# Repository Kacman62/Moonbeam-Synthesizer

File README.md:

# MoonBeam Synthesizer
A standalone DAWLESS synthesizer based on a Raspberry Pi Pico. Includes a custom circuit board and codebase with the Mozzi Audio Library

# Features

- 25 multiplexed piano style keys
- Support for up to 5 notes at the same time
- 3 Analog sliders for volume pitch and vibrato
- OLED display and 2 rotary encoders with a custom code base
- Sound synthesis using the Mozzi audio library
- 4 different wave forms
- Custom ADSR editing
- Oscilloscope style waveform viewer
- Toggleable speaker and headphone out
- Audio effects and filters
- Preset sound fforms

# Initial Idea
After reading the guide from Hack club and others online to make a MIDI keyboard, it seemed like a great idea. After more research though I wanted a standalone synthesizer that does not need a computer and couldn't find many examples online. This seemed like it would be easy enough so I decided to do it myself

# Schematic and Board
The whole project is built around a raspberry pi pico 1 (a pico 2 should work too but untested). A 5x5 multiplexed array of key cap switches serve as the main input. 
On the Audio side, a PCM5100 I2S DAC is channeled into a LM4810 and LM4861 audio amplifiers, that go to a speaker and headphone jack.

The PCB was a lot more challenging, just due to the sheer size of it. It ends up being about 350mm x 90mm. But the routing wasn't too hard and I like the look of how it turned out

# Case Design
There is an included case. Currently I have not received the board so I can not confirm if it works perfectly, but I designed it around the 3D cad of the board so it should work fine. 
Only 1 of each file needs to be printed and it is assembled using M4 hardware

# Software
I initially dreaded the software but it ended up being very fun after the initial hurdles. The code is split into 2 cores, 1 for audio and 1 for the digital UI. It should work with the final assembly, all the digital has been tested, but the audio is using I2S which I can't test currently. I did use it a little bit with PWM audio and that worked fine. The waveform viewer also does show an audio signal so Im pretty confident that it will work

# UI
You navigate the UI with both rotary encoders. Double clicking either brings you into the main menu. Rotate either to select an app.
* Settings (Wrench): View current notes on each audio voice and the values of the slide potentiometers
* ADSR Editor (Envelope): Use one dial to change the level of the ADSR and the other to change the time. Changing the level of the decay, sustain and release will change the other two with it. this is intended to avoid weird audio clipping
* Wave Viewer (Wave): View the current outputted wave form. Automatically adjusts the zoom if multiple voices are playing
* Wave Changer (Square Wave): Choose from either a sin, triangle, saw, or square wave

# Art
All pixel art was created by me using Aseprite. The PK Industries and the Moonbeam synth logo are unregistered trademarks, not real companies and products, and have no legal binding on anything. I am not a lawyer, and this joke has gone on too long.

# Disclaimers
If you want to know more about the design and build process check out the journal

This project is sponsored by and made in collaboration with Hack Club, go check them out

Consider this project untested. I have put my full effort into this project and fully believe that it will work, but I have not received boards yet and thus do not know if this will work first try

# Hack Club Stuff

Estimate Total Hours: 48

My Final Total: 60.31

Your Final Total: 96.73

https://blueprint.hackclub.com/projects/928 

# Update 11/11

Huge thanks to Hack Club and the Blueprint program for assisting in this project. I have now received funding for the project and will be ordering parts. Expect future updates at the start of December

# Update 11/25

Boards have been received. Still waiting on LCSC order. Small errors have been found in the board and have been fixed in the PCB files

# Update 12/1

Boards have been assembled and multiple errors have been found. The files will still be up, but assume they do not work.
Nothing shorts together, but both the button matrix is broken, as well as the I2S DAC and amplifier not working.

# Update 12/3

After reflowing the baord, the issue has been fixed. Two of the data lines into the DAC were shorted and after fixing that, it makes sound. The code still has some issues, but they are being fixed rapidly and the current board is almost done.

# Update 12/4 

This project is now shipped. I had a lot of fun working on this, and will continue to update the software, but for now the project is in a working state so expect less updates.

# Update 12/12 

Version 1 of software is now released. This features upgrades to all parts of the code base. Numerous bug fixes, rewritten audio workflow. Support for filters, effects, and presets. Improved menus and clarity. 

# Known issues

Code: 

In settings, the note played is incorrect (going to wait for boards to arrive so I can assign keys different notes) Fixed 12/12/25

Button scanning matrix is incorrect, every button plays the same 5 notes FIXED 12/3/25

In Wave changer, the picture of the sawtooth wave is reversed from what is seen in the wave viewer

In Wave Viewer, the wave slides around randomly. (The wave is still representative of what the audio out looks like, it's just hard to focus on it)

Distortion effect is unstable and clips audio most of the time. Still able to be used in code, but not recomended

Board:

Slide pot pin spacing 2.00mm instead of 2.54mm FIXED 11/25/25

Resistor footprint 7.62mm instead of 12.04mm FIXED 11/25/25

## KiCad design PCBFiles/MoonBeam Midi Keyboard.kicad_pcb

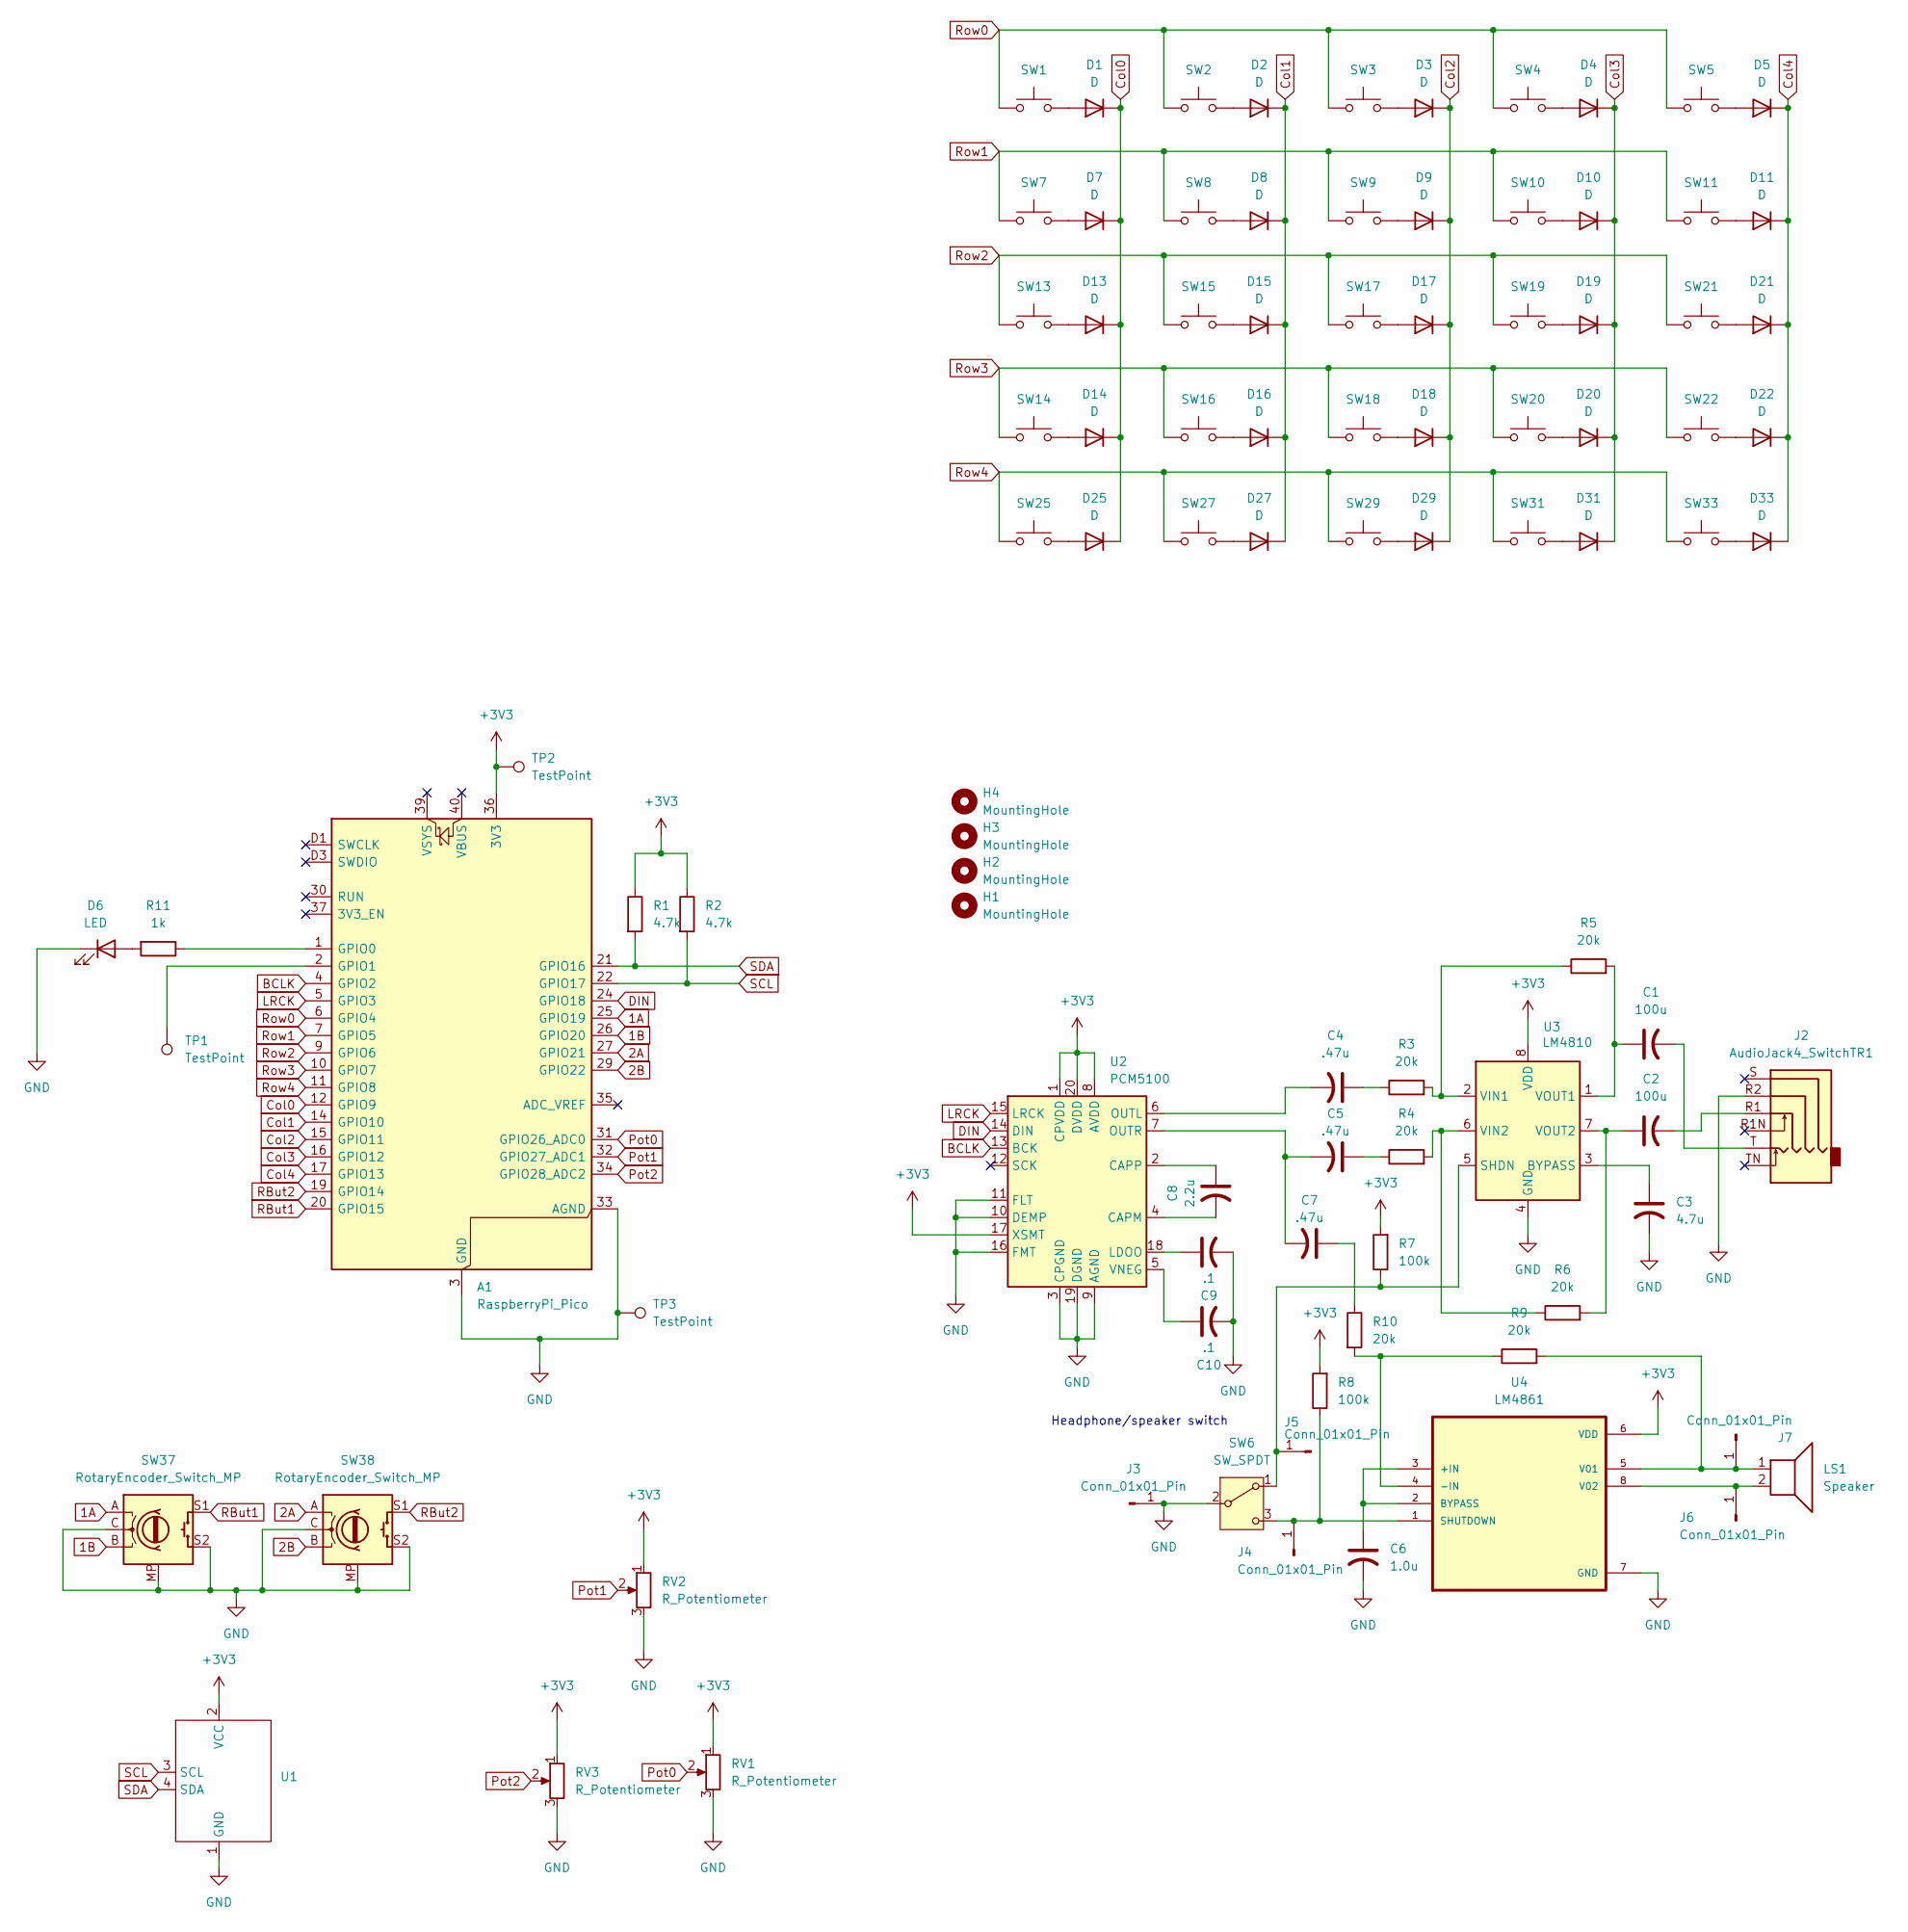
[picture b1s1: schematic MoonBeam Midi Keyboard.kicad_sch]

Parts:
A1: RaspberryPi_Pico; RaspberryPi_Pico_Common_THT
C1, C2: 100u; CP_Radial_D5.0mm_P2.50mm
C3: 4.7u; CP_Radial_D5.0mm_P2.50mm
C4, C5, C7: .47u; CP_Radial_D5.0mm_P2.50mm
C6: 1.0u; CP_Radial_D5.0mm_P2.50mm
C8: 2.2u; CP_Radial_D5.0mm_P2.50mm
C9, C10: .1; CP_Radial_D5.0mm_P2.50mm
D1, D2, D3, D4, D5, D7, D8, D9, D10, D11, D13, D14, D15, D16, D17, D18, D19, D20, D21, D22, D25, D27, D29, D31, D33: D; D_DO-35_SOD27_P7.62mm_Horizontal
D6: LED; LED_D3.0mm
H1, H2, H3: MountingHole; MountingHole_4.3mm_M4
H4: MountingHole; MountingHole_4.3mm_M4_DIN965
J2: AudioJack4_SwitchTR1; Jack_3.5mm_PJ31060-I_Horizontal
J3, J4, J5, J6, J7: Conn_01x01_Pin; TestPoint_Pad_4.0x4.0mm
LS1: Speaker
R1, R2: 4.7k; R_Axial_DIN0207_L6.3mm_D2.5mm_P10.16mm_Horizontal
R3, R4, R5, R6, R9, R10: 20k; R_Axial_DIN0207_L6.3mm_D2.5mm_P10.16mm_Horizontal
R7, R8: 100k; R_Axial_DIN0207_L6.3mm_D2.5mm_P10.16mm_Horizontal
R11: 1k; R_Axial_DIN0207_L6.3mm_D2.5mm_P10.16mm_Horizontal
RV1, RV2, RV3: R_Potentiometer; Slide Pot
SW1, SW2, SW3, SW4, SW5, SW7, SW8, SW9, SW10, SW11, SW13, SW14, SW15, SW16, SW17, SW18, SW19, SW20, SW21, SW22, SW25, SW27, SW29, SW31, SW33: SW_Omron_B3FS; SW_Cherry_MX_1.00u_PCB
SW6: SW_SPDT
SW37, SW38: RotaryEncoder_Switch_MP; RotaryEncoder_Alps_EC11E-Switch_Vertical_H20mm_MountingHoles
TP1, TP2, TP3: TestPoint; TestPoint_Pad_4.0x4.0mm
U1: 0.96 OLED I2C
U2: PCM5100; TSSOP-20_4.4x6.5mm_P0.65mm
U3: LM4810; TSSOP-8_3x3mm_P0.65mm
U4: LM4861; SOIC127P600X175-8N

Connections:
1A: A1.25 (GPIO19), SW37.A
1B: A1.26 (GPIO20), SW37.B
2A: A1.27 (GPIO21), SW38.A
2B: A1.29 (GPIO22), SW38.B
+3V3: A1.36 (3V3), R1.1, R2.1, R7.2, R8.2, RV1.1, RV2.1, RV3.1, TP2.1, U1.2 (VCC), U2.1 (CPVDD), U2.8 (AVDD), U2.17 (XSMT), U2.20 (DVDD), U3.8 (VDD), U4.6 (VDD); also elsewhere on the board
BCLK: A1.4 (GPIO2), U2.13 (BCK)
Col0: A1.12 (GPIO9), D1.1 (K), D7.1 (K), D13.1 (K), D14.1 (K), D25.1 (K)
Col1: A1.14 (GPIO10), D2.1 (K), D8.1 (K), D15.1 (K), D16.1 (K), D27.1 (K)
Col2: A1.15 (GPIO11), D3.1 (K), D9.1 (K), D17.1 (K), D18.1 (K), D29.1 (K)
Col3: A1.16 (GPIO12), D4.1 (K), D10.1 (K), D19.1 (K), D20.1 (K), D31.1 (K)
Col4: A1.17 (GPIO13), D5.1 (K), D11.1 (K), D21.1 (K), D22.1 (K), D33.1 (K)
DIN: A1.24 (GPIO18), U2.14 (DIN)
GND: A1.3 (GND), A1.8 (GND), A1.13 (GND), A1.18 (GND), A1.23 (GND), A1.28 (GND), A1.33 (AGND), A1.38 (GND), A1.D2 (GND), C3.2, C6.2, C9.2, C10.2, D6.1 (K), J2.R2, J3.1, RV1.3, RV2.3, RV3.3, SW6.2 (B), SW37.C, SW37.MP, SW37.S2, SW38.C, SW38.MP, SW38.S2, TP3.1, U1.1 (GND), U2.3 (CPGND), U2.9 (AGND), U2.10 (DEMP), U2.11 (FLT), U2.16 (FMT), U2.19 (DGND), U3.4 (GND), U4.7 (GND); also elsewhere on the board
LRCK: A1.5 (GPIO3), U2.15 (LRCK)
unnamed: A1.1 (GPIO0), R11.1
unnamed 15: A1.2 (GPIO1), TP1.1; also elsewhere on the board
unnamed: C1.2, J2.T
unnamed: C2.2, J2.R1
unnamed: C4.1, R3.1
unnamed: C5.1, R4.1
unnamed: C7.1, R10.1
unnamed: D1.2 (A), SW1.2
unnamed: D2.2 (A), SW2.2
unnamed: D3.2 (A), SW3.2
unnamed: D4.2 (A), SW4.2
unnamed: D5.2 (A), SW5.2
unnamed: D6.2 (A), R11.2
unnamed: D7.2 (A), SW7.2
unnamed: D8.2 (A), SW8.2
unnamed: D9.2 (A), SW9.2
unnamed: D10.2 (A), SW10.2
unnamed: D11.2 (A), SW11.2
unnamed: D13.2 (A), SW13.2
unnamed: D14.2 (A), SW14.2
unnamed: D15.2 (A), SW15.2
unnamed: D16.2 (A), SW16.2
unnamed: D17.2 (A), SW17.2
unnamed: D18.2 (A), SW18.2
unnamed: D19.2 (A), SW19.2
unnamed: D20.2 (A), SW20.2
unnamed: D21.2 (A), SW21.2
unnamed: D22.2 (A), SW22.2
unnamed: D25.2 (A), SW25.2
unnamed: D27.2 (A), SW27.2
unnamed: D29.2 (A), SW29.2
unnamed: D31.2 (A), SW31.2
unnamed: D33.2 (A), SW33.2
unnamed: J4.1, R8.1, SW6.3 (C), U4.1 (SHUTDOWN)
unnamed: J5.1, R7.1, SW6.1 (A), U3.5 (SHDN)
unnamed: J6.1, LS1.2, U4.8 (V02)
unnamed: J7.1, LS1.1, R9.2, U4.5 (V01)
unnamed: C8.2, U2.4 (CAPM)
unnamed: C8.1, U2.2 (CAPP)
unnamed: C9.1, U2.18 (LDOO)
unnamed: C4.2, U2.6 (OUTL)
unnamed: C5.2, C7.2, U2.7 (OUTR)
unnamed: C10.1, U2.5 (VNEG)
unnamed: C3.1, U3.3 (BYPASS)
unnamed: R3.2, R5.1, U3.2 (VIN1)
unnamed: R4.2, R6.1, U3.6 (VIN2)
unnamed: C1.1, R5.2, U3.1 (VOUT1)
unnamed: C2.1, R6.2, U3.7 (VOUT2)
unnamed: C6.1, U4.2 (BYPASS), U4.3 (+IN)
unnamed: R9.1, R10.2, U4.4 (-IN)
Pot0: A1.31 (GPIO26_ADC0), RV1.2
Pot1: A1.32 (GPIO27_ADC1), RV2.2
Pot2: A1.34 (GPIO28_ADC2), RV3.2
RBut1: A1.20 (GPIO15), SW37.S1
RBut2: A1.19 (GPIO14), SW38.S1
Row0: A1.6 (GPIO4), SW1.1, SW2.1, SW3.1, SW4.1, SW5.1
Row1: A1.7 (GPIO5), SW7.1, SW8.1, SW9.1, SW10.1, SW11.1
Row2: A1.9 (GPIO6), SW13.1, SW15.1, SW17.1, SW19.1, SW21.1
Row3: A1.10 (GPIO7), SW14.1, SW16.1, SW18.1, SW20.1, SW22.1
Row4: A1.11 (GPIO8), SW25.1, SW27.1, SW29.1, SW31.1, SW33.1
SCL: A1.22 (GPIO17), R2.2, U1.3 (SCL)
SDA: A1.21 (GPIO16), R1.2, U1.4 (SDA)

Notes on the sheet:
Headphone/speaker switch

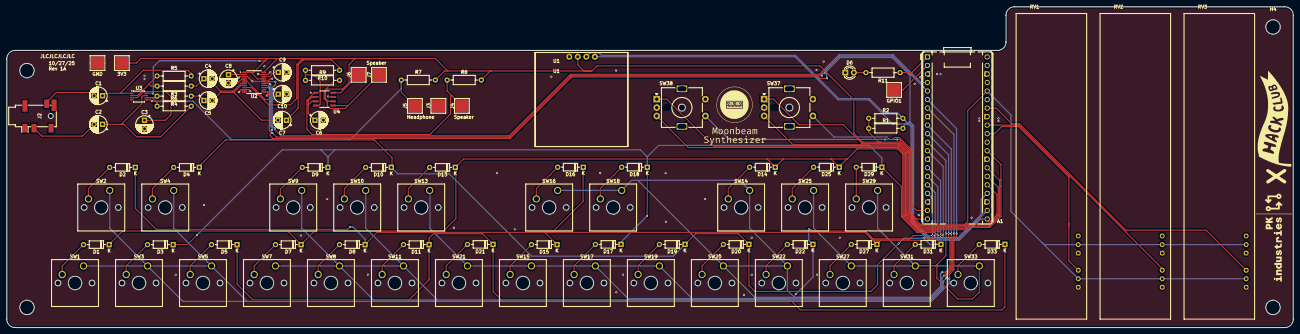
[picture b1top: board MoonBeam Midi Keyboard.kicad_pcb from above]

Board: 2 copper layers, 383.0 x 95.5 mm, 95 parts (0 on the bottom side), 76 nets.

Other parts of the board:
3V3: Conn_01x01_Pin; TestPoint_Pad_4.0x4.0mm
GND: Conn_01x01_Pin; TestPoint_Pad_4.0x4.0mm
GPIO1: Conn_01x01_Pin; TestPoint_Pad_4.0x4.0mm

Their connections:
+3V3: 3V3.1; also elsewhere on the board
GND: GND.1; also elsewhere on the board
unnamed 15: GPIO1.1; also elsewhere on the board

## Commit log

2025-11-26 added updated PCB files
2025-11-26 Add project updates and board issue fixes
    Added updates regarding project funding and board issues.
2025-12-03 Update README with DAC fix and board status
    Added update regarding DAC issue resolution and current status.
2025-12-03 Update README with known issues
    Added known issues section with details on code and board problems.
2025-12-04 optimized and fixed audio side of code
2025-12-04 optimized audio side
2025-12-04 staging commits
2025-12-04 fixed mergin issues
2025-12-12 Version 1 of software upload
2025-12-12 Update README with version 1 release notes
    Added updates about software version 1 release and bug fixes.
